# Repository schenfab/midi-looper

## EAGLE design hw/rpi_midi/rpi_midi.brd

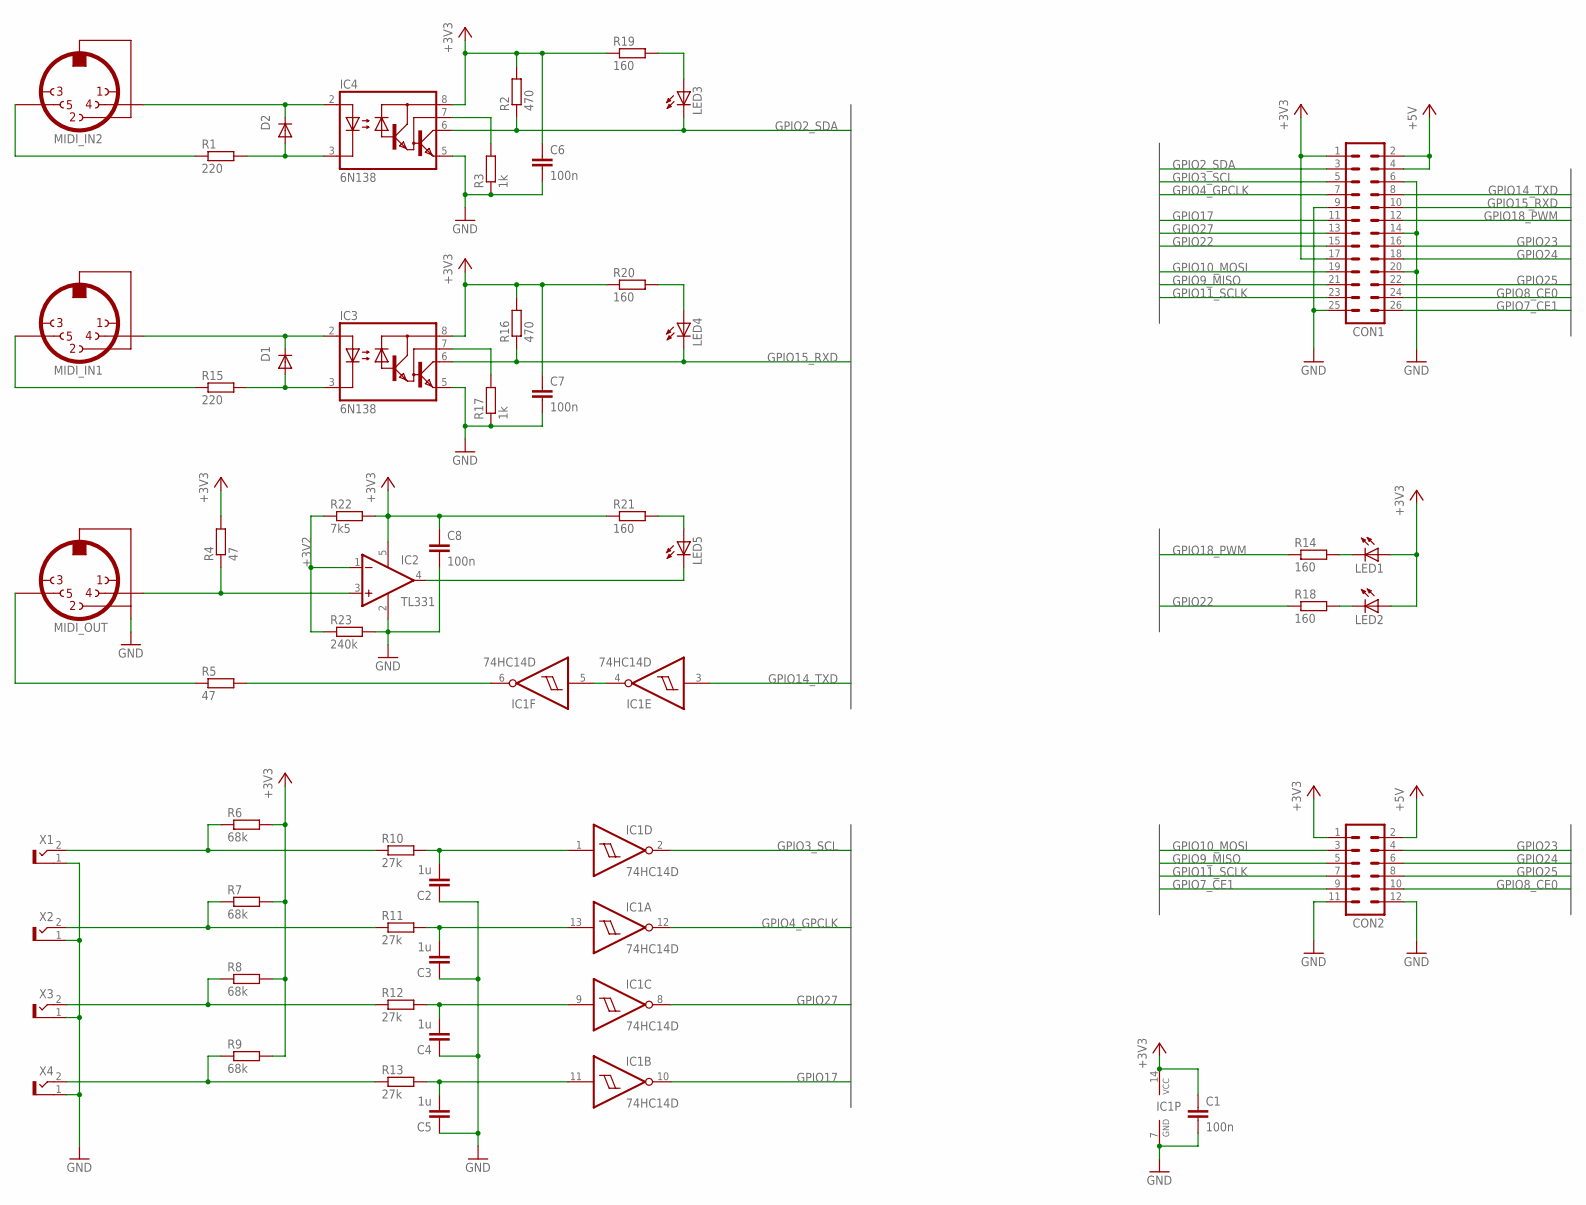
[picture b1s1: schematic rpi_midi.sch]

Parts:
C1, C6, C7, C8: 100n; C0603
C2, C3, C4, C5: 1u; C0603
CON1: MA13-2
CON2: MA06-2
D1, D2: 1N4148SOD-323; SOD323-R
IC1: 74HC14D; SO14
IC2: TL331; SOT23-DBV
IC3, IC4: 6N138; DIL08
LED1, LED2, LED3, LED4, LED5: LED2.54MM; HEADER_2X1
MIDI_IN1, MIDI_IN2: MIDI_2PIN; HEADER_2X1
MIDI_OUT: MIDI_3PIN; HEADER_3X1
R1, R15: 220; R0603
R2, R16: 470; R0603
R3, R17: 1k; R0603
R4, R5: 47; R0603
R6, R7, R8, R9: 68k; R0603
R10, R11, R12, R13: 27k; R0603
R14, R18, R19, R20, R21: 160; R0603
R22: 7k5; R0603
R23: 240k; R0603
X1, X2, X3, X4: WBTOR12.54MM; HEADER_2X1

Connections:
+3V2: IC2.1 (-IN), R22.1, R23.1
+3V3: C1.1, C6.1, C7.1, C8.1, CON1.1, CON1.17, CON2.1, IC1.14 (VCC), IC2.5 (V+), IC3.8 (VCC), IC4.8 (VCC), LED1.1 (A), LED2.1 (A), R2.2, R4.2, R6.2, R7.2, R8.2, R9.2, R16.2, R19.1, R20.1, R21.1, R22.2
+5V: CON1.2, CON1.4, CON2.2
GND: C1.2, C2.1, C3.1, C4.1, C5.1, C6.2, C7.2, C8.2, CON1.6, CON1.9, CON1.14, CON1.20, CON1.25, CON2.11, CON2.12, IC1.7 (GND), IC2.2 (V-), IC3.5 (GND), IC4.5 (GND), MIDI_OUT.3 (PE), R3.1, R17.1, R23.2, X1.1 (S), X2.1 (S), X3.1 (S), X4.1 (S)
GPIO2_SDA: CON1.3, IC4.6 (VO), LED3.2 (C), R2.1
GPIO3_SCL: CON1.5, IC1.2 (O)
GPIO4_GPCLK: CON1.7, IC1.12 (O)
GPIO7_CE1: CON1.26, CON2.9
GPIO8_CE0: CON1.24, CON2.10
GPIO9_MISO: CON1.21, CON2.5
GPIO10_MOSI: CON1.19, CON2.3
GPIO11_SCLK: CON1.23, CON2.7
GPIO14_TXD: CON1.8, IC1.3 (I)
GPIO15_RXD: CON1.10, IC3.6 (VO), LED4.2 (C), R16.1
GPIO17: CON1.11, IC1.10 (O)
GPIO18_PWM: CON1.12, R14.1
GPIO22: CON1.15, R18.1
GPIO23: CON1.16, CON2.4
GPIO24: CON1.18, CON2.6
GPIO25: CON1.22, CON2.8
GPIO27: CON1.13, IC1.8 (O)
unnamed: MIDI_IN2.2 (5), R1.1
unnamed: D2.A, IC4.3 (C), R1.2
unnamed: D2.C, IC4.2 (A), MIDI_IN2.1 (4)
unnamed: LED1.2 (C), R14.2
unnamed: IC4.7 (VB), R3.2
unnamed: IC1.6 (O), R5.2
unnamed: LED2.2 (C), R18.2
unnamed: IC1.4 (O), IC1.5 (I)
unnamed: MIDI_OUT.2 (5), R5.1
unnamed: IC2.3 (+IN), MIDI_OUT.1 (4), R4.1
unnamed: MIDI_IN1.2 (5), R15.1
unnamed: R6.1, R10.1, X1.2 (T)
unnamed: C2.2, IC1.1 (I), R10.2
unnamed: R7.1, R11.1, X2.2 (T)
unnamed: R8.1, R12.1, X3.2 (T)
unnamed: R9.1, R13.1, X4.2 (T)
unnamed: C3.2, IC1.13 (I), R11.2
unnamed: C4.2, IC1.9 (I), R12.2
unnamed: C5.2, IC1.11 (I), R13.2
unnamed: D1.A, IC3.3 (C), R15.2
unnamed: IC2.4 (OUT), LED5.2 (C)
unnamed: LED5.1 (A), R21.2
unnamed: D1.C, IC3.2 (A), MIDI_IN1.1 (4)
unnamed: IC3.7 (VB), R17.2
unnamed: LED3.1 (A), R19.2
unnamed: LED4.1 (A), R20.2

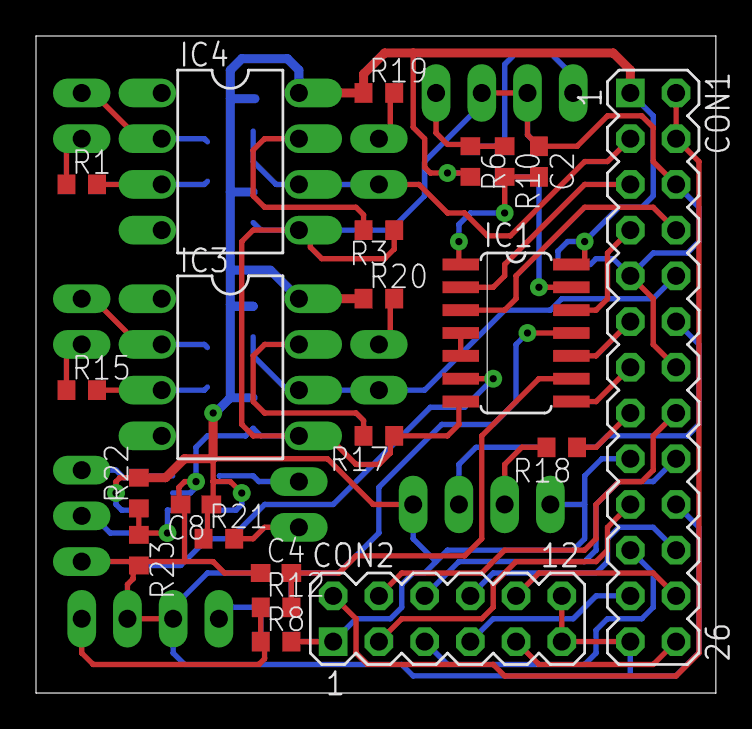
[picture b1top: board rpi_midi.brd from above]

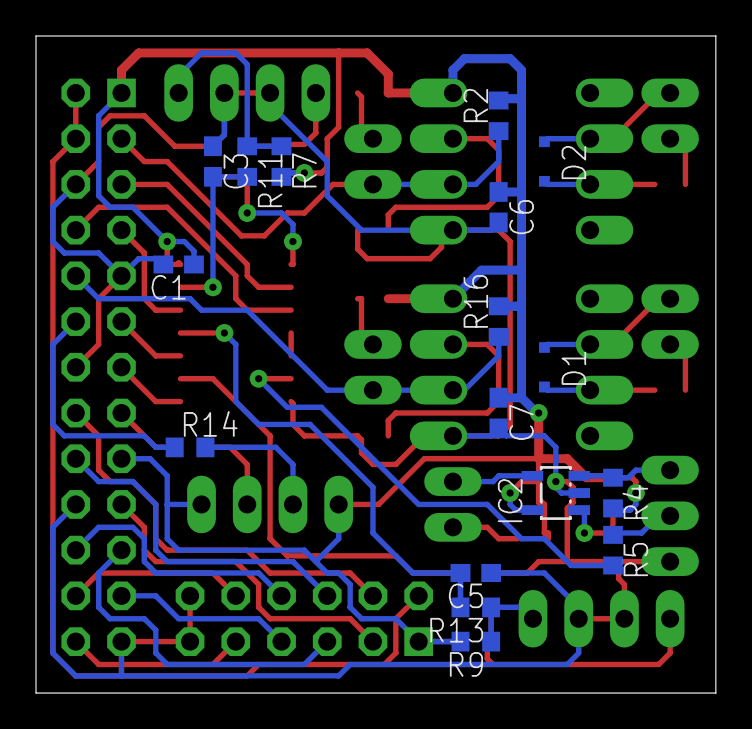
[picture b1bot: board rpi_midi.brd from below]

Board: 2 copper layers, 37.8 x 36.5 mm, 51 parts (17 on the bottom side), 47 nets.

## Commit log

2012-10-30 Modified global .gitignore to ignore *~ and *.o
2012-10-30 Added hello_world software example
2012-10-30 Added gpio_example software example.
    The gpio access is done directly over /dev/mmap.
2012-10-30 Added archlinux kernel configs: config-arch: original config-arch-rs-2012-10-29: modified
2012-10-30 Added github.com/raspberrypi/linux.git as submodule to kernel/raspi-linux
2012-12-11 Added the schematic file for the RPi MIDI extension board
2012-12-16 The RPi MIDI extension board now features MIDI_OUT link detection capabilities
2013-01-03 Added the most recent PCB schematic and layout files
2013-01-09 Updated the RPi MIDI hardware layout file with a silkscreen layer
2013-01-17 Updated the MIDI extension hardware layout file. Optimized the routing of several signals to avoid sharp-angled fanouts
2013-01-21 Added alsa_midi program. It shows how to probe for midi ports and how to receive and send midi commands over the alsa raw midi interface.
2013-01-28 Added gerber-files for the production of the PCB v1.0
